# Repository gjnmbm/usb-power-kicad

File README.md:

# usb-power-kicad
A KiCAD project that would allow one to provide external power to USB devices via a power jack using USB 3.0.

## Note: 

CAM files reflect revision 2 of this board, so if you want to use CAM files when ordering a PCB, you will need to export the current revision of this board into the files you need.

The footprint I used from Ultra Librarian was wrong for the female USB 3.0 A connector, so I had to make changes to it following what the datasheet said.
The footprint I edited has hopefully been added to this repository.

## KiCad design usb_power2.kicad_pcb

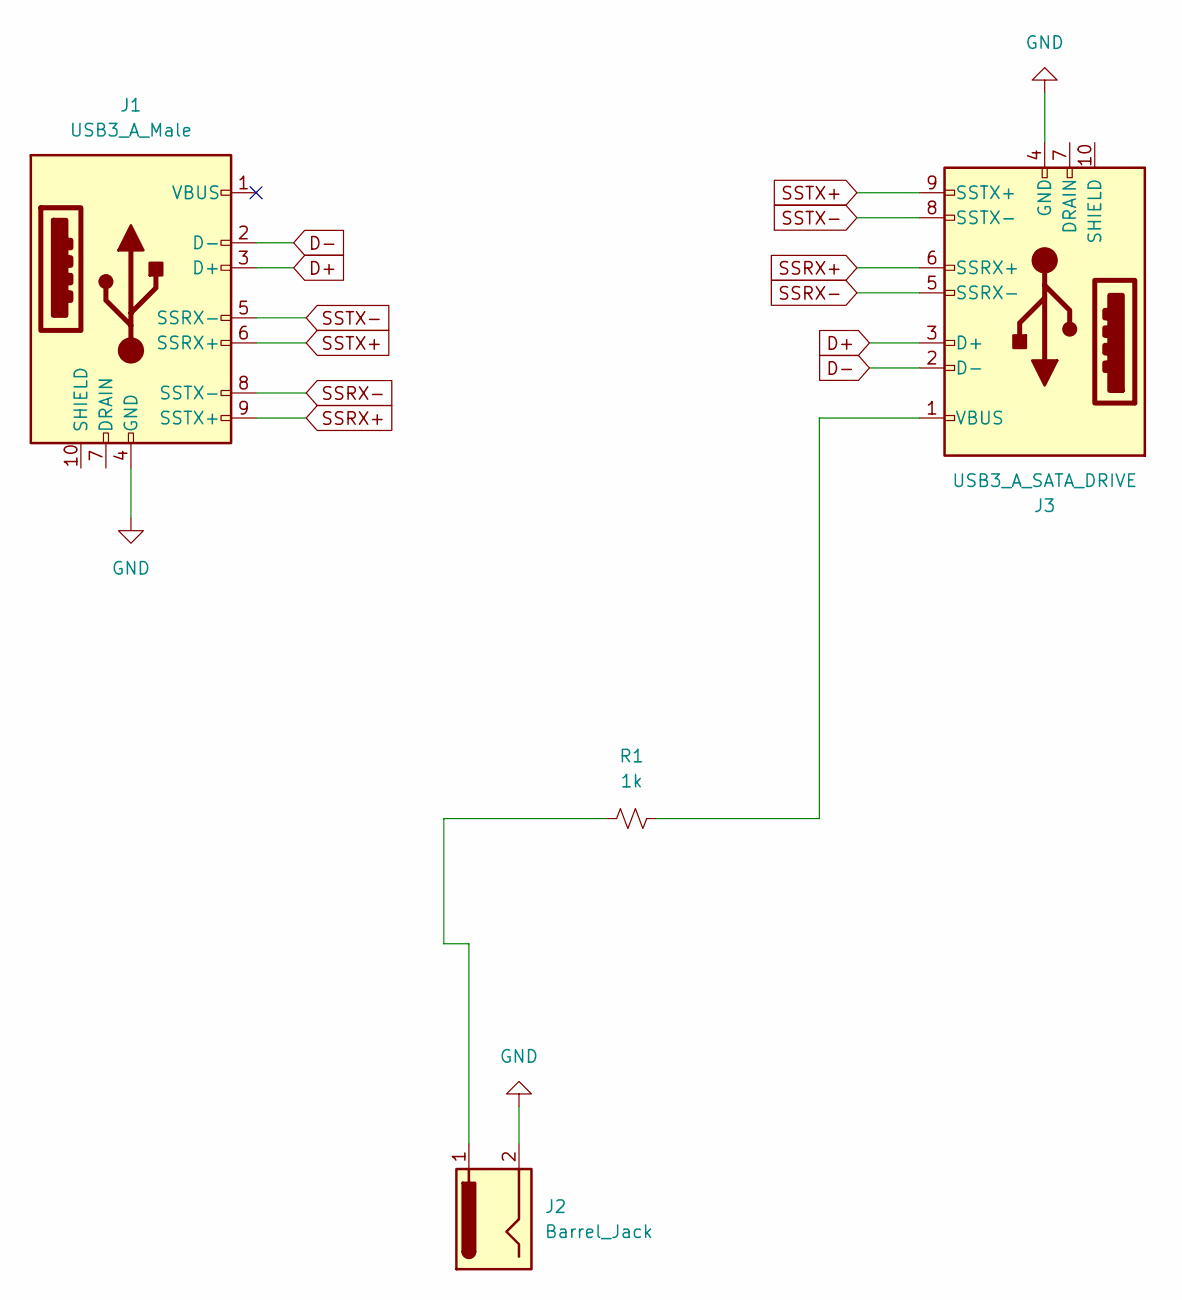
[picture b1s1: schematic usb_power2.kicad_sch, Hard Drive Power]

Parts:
J1: USB3_A_Male; ASSMANN_A-USB3_A-LP-SMT1; Digikey Part Number AE10703-ND
J2: Barrel_Jack; BarrelJack_Horizontal
J3: USB3_A_SATA_DRIVE; AU-Y1006-3; Digikey Part Number AE10704-ND
R1: 1k; R_Axial_DIN0207_L6.3mm_D2.5mm_P2.54mm_Vertical

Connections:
D+: J1.3 (D+), J3.3 (D+)
D-: J1.2 (D-), J3.2 (D-)
GND: J1.4 (GND), J2.2, J3.4 (GND)
unnamed: J2.1, R1.1
unnamed: J3.1 (VBUS), R1.2
SSRX+: J1.9 (SSTX+), J3.6 (SSRX+)
SSRX-: J1.8 (SSTX-), J3.5 (SSRX-)
SSTX+: J1.6 (SSRX+), J3.9 (SSTX+)
SSTX-: J1.5 (SSRX-), J3.8 (SSTX-)

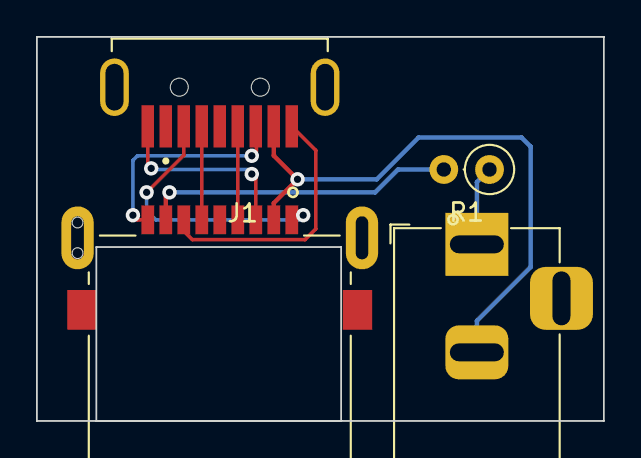
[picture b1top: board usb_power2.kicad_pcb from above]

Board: 2 copper layers, 31.5 x 21.3 mm, 4 parts (0 on the bottom side), 9 nets.

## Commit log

2022-12-31 Add corrected UL female 3.0 USB A footprint
2022-12-31 Updated Footprint
